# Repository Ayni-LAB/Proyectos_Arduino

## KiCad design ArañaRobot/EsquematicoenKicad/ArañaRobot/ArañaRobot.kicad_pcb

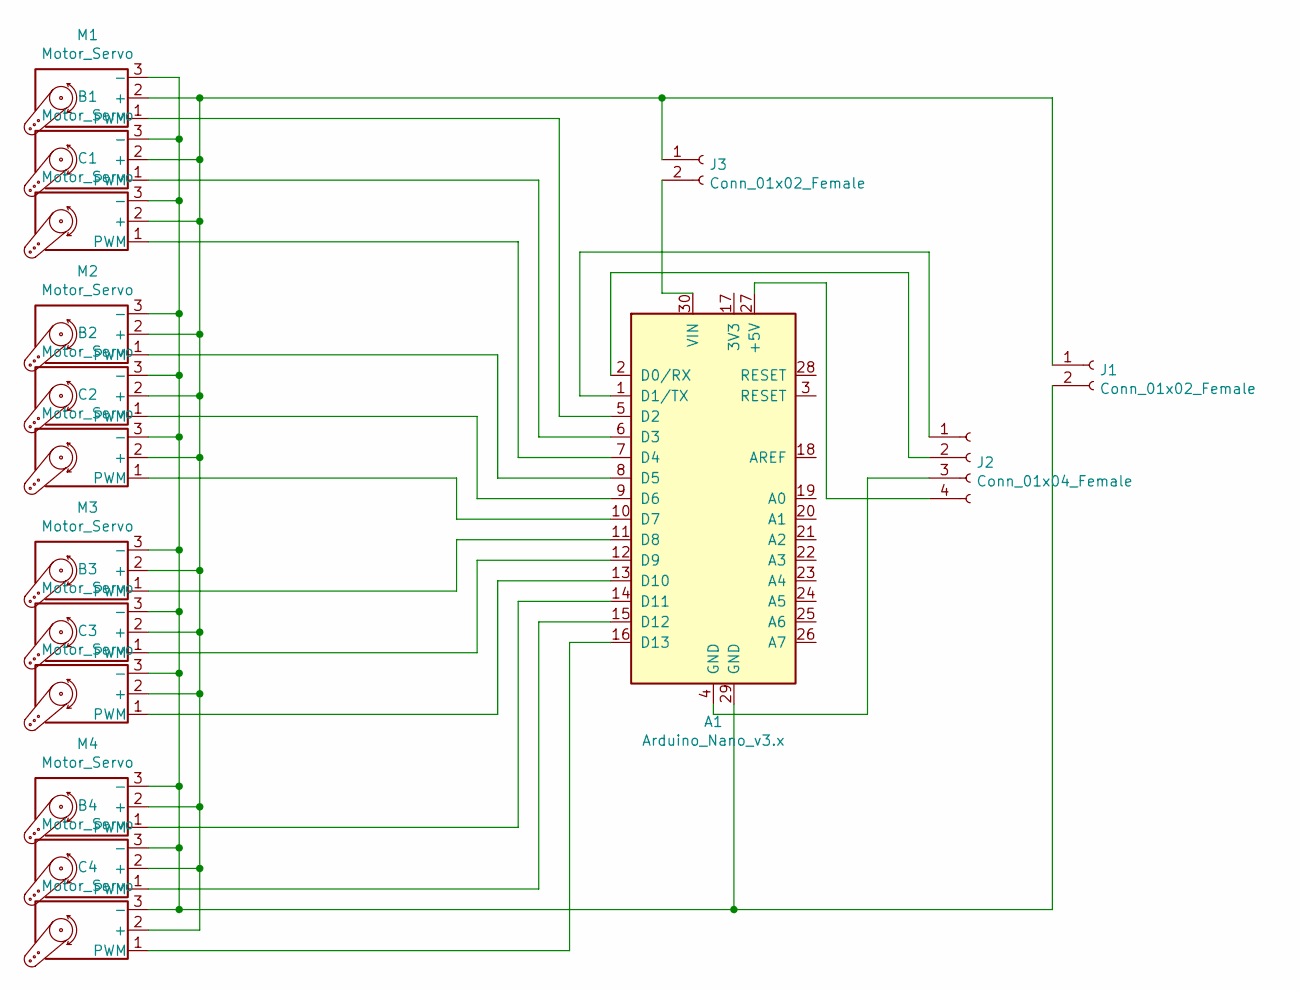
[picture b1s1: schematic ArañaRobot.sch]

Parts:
A1: Arduino_Nano_v3.x; Arduino_Nano
B1, B2, B3, B4: Motor_Servo; PinHeader_1x03_P2.54mm_Vertical
C1, C2, C3, C4: Motor_Servo; PinHeader_1x03_P2.54mm_Vertical
J1: Conn_01x02_Female; PhoenixContact_GMSTBA_2,5_2-G-7,62_1x02_P7.62mm_Horizontal
J2: Conn_01x04_Female; FanPinHeader_1x04_P2.54mm_Vertical
J3: Conn_01x02_Female; PinHeader_1x02_P2.00mm_Vertical
M1, M2, M3, M4: Motor_Servo; PinHeader_1x03_P2.54mm_Vertical

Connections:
unnamed: A1.1 (D1/TX), J2.1
unnamed: A1.2 (D0/RX), J2.2
unnamed: A1.4 (GND), J2.3
unnamed: A1.5 (D2), M1.1 (PWM)
unnamed: A1.6 (D3), B1.1 (PWM)
unnamed: A1.7 (D4), C1.1 (PWM)
unnamed: A1.8 (D5), M2.1 (PWM)
unnamed: A1.9 (D6), B2.1 (PWM)
unnamed: A1.10 (D7), C2.1 (PWM)
unnamed: A1.11 (D8), M3.1 (PWM)
unnamed: A1.12 (D9), B3.1 (PWM)
unnamed: A1.13 (D10), C3.1 (PWM)
unnamed: A1.14 (D11), M4.1 (PWM)
unnamed: A1.15 (D12), B4.1 (PWM)
unnamed: A1.16 (D13), C4.1 (PWM)
unnamed: A1.27 (+5V), J2.4
unnamed: A1.29 (GND), B1.3 (-), B2.3 (-), B3.3 (-), B4.3 (-), C1.3 (-), C2.3 (-), C3.3 (-), C4.3 (-), J1.2, M1.3 (-), M2.3 (-), M3.3 (-), M4.3 (-)
unnamed: A1.30 (VIN), J3.2
unnamed: B1.2 (+), B2.2 (+), B3.2 (+), B4.2 (+), C1.2 (+), C2.2 (+), C3.2 (+), C4.2 (+), J1.1, J3.1, M1.2 (+), M2.2 (+), M3.2 (+), M4.2 (+)

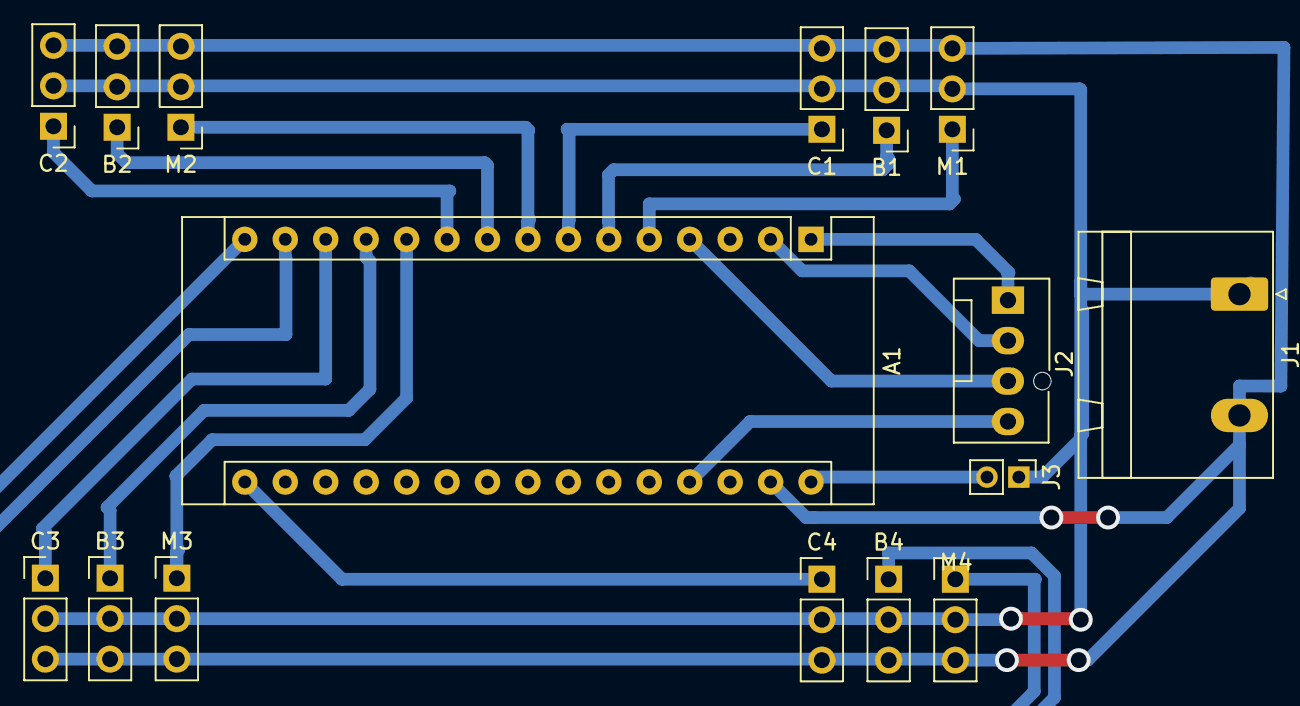
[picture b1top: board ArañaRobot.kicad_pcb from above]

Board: 2 copper layers, 16 parts (0 on the bottom side), 19 nets.

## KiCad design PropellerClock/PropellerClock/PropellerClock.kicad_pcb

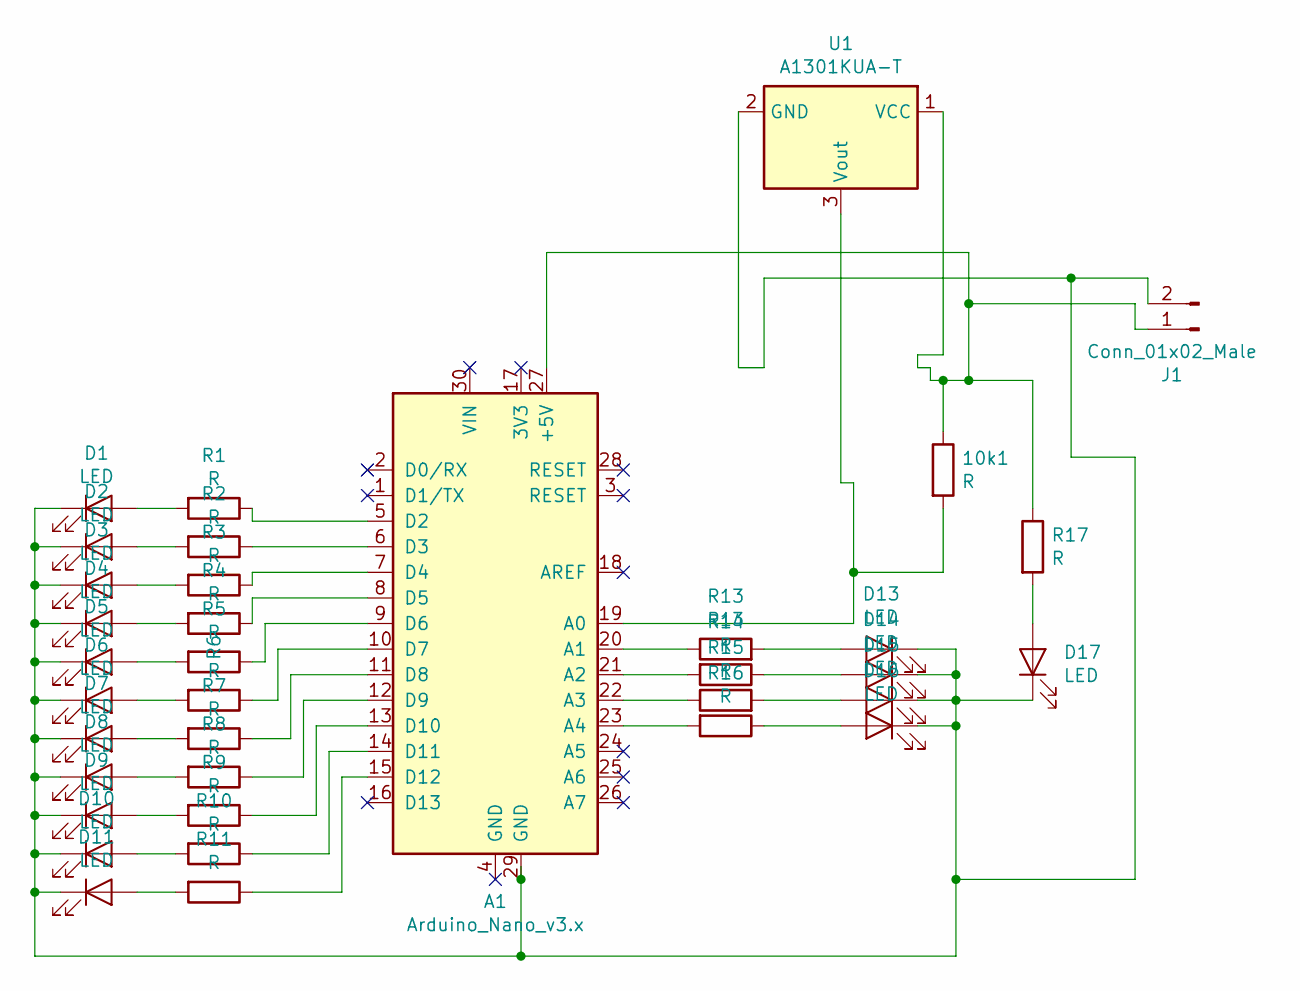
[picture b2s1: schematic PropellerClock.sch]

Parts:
10k1: R; R_Axial_DIN0204_L3.6mm_D1.6mm_P7.62mm_Horizontal
A1: Arduino_Nano_v3.x; Arduino_Nano
D1, D2, D3, D4, D5, D6, D7, D8, D9, D10, D11, D13, D14, D15, D16, D17: LED; LED_D5.0mm
J1: Conn_01x02_Male; PinHeader_1x02_P2.00mm_Vertical
R1, R2, R3, R4, R5, R6, R7, R8, R9, R10, R11, R14, R15, R16, R17: R; R_Axial_DIN0204_L3.6mm_D1.6mm_P7.62mm_Horizontal
R13: R13; R_Axial_DIN0204_L3.6mm_D1.6mm_P7.62mm_Horizontal
U1: A1301KUA-T; PinHeader_1x03_P1.27mm_Vertical

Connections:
unnamed: 10k1.1, A1.27 (+5V), J1.1, R17.1, U1.1 (VCC)
unnamed: 10k1.2, A1.19 (A0), U1.3 (Vout)
unnamed: A1.5 (D2), R1.1
unnamed: A1.6 (D3), R2.1
unnamed: A1.7 (D4), R3.1
unnamed: A1.8 (D5), R4.1
unnamed: A1.9 (D6), R5.1
unnamed: A1.10 (D7), R6.1
unnamed: A1.11 (D8), R7.1
unnamed: A1.12 (D9), R8.1
unnamed: A1.13 (D10), R9.1
unnamed: A1.14 (D11), R10.1
unnamed: A1.15 (D12), R11.1
unnamed: A1.20 (A1), R13.1
unnamed: A1.21 (A2), R14.2
unnamed: A1.22 (A3), R15.1
unnamed: A1.23 (A4), R16.2
unnamed: A1.29 (GND), D1.1 (K), D2.1 (K), D3.1 (K), D4.1 (K), D5.1 (K), D6.1 (K), D7.1 (K), D8.1 (K), D9.1 (K), D10.1 (K), D11.1 (K), D13.1 (K), D14.1 (K), D15.1 (K), D16.1 (K), D17.1 (K), J1.2, U1.2 (GND)
unnamed: D1.2 (A), R1.2
unnamed: D2.2 (A), R2.2
unnamed: D3.2 (A), R3.2
unnamed: D4.2 (A), R4.2
unnamed: D5.2 (A), R5.2
unnamed: D6.2 (A), R6.2
unnamed: D7.2 (A), R7.2
unnamed: D8.2 (A), R8.2
unnamed: D9.2 (A), R9.2
unnamed: D10.2 (A), R10.2
unnamed: D11.2 (A), R11.2
unnamed: D13.2 (A), R13.2
unnamed: D14.2 (A), R14.1
unnamed: D15.2 (A), R15.2
unnamed: D16.2 (A), R16.1
unnamed: D17.2 (A), R17.2

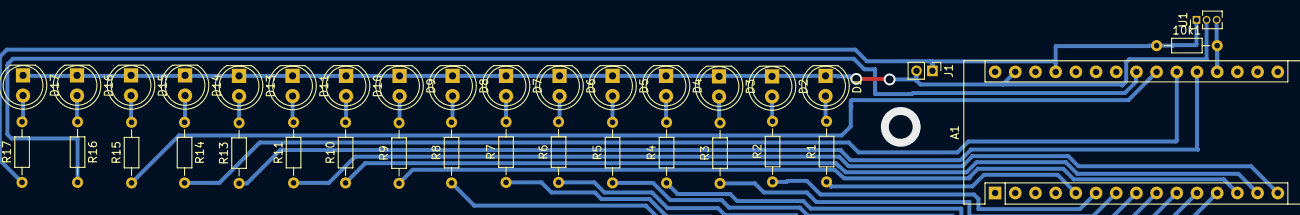
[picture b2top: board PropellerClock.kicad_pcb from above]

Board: 2 copper layers, 36 parts (0 on the bottom side), 34 nets.

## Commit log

2020-03-02 inicio
2020-03-02 1 modificacion readme
2020-03-02 1 modificacion codigo araña
2020-03-02 Comentarios Araña
2020-03-02 Cambio en comentarios
2020-03-02 Camb. Lagarto
2020-03-02 modificaciones Br
2020-03-02 prueba de contri
2020-03-02 Prueba commit
2020-03-02 Commibrig
2020-03-02 modificaciones bases
2020-03-03 Proyecto nuevo
2020-03-03 AgregandoFotos
2020-03-03 Readme modificado
2020-03-03 Readme imagenes
2020-03-03 readme configurations
2020-03-03 Readme1
2020-03-03 Readme3
2020-03-03 Readme4
2020-03-03 Readme
2020-03-03 Readme5
2020-03-11 Primer commit
2020-03-11 Propeller prototipo
2020-03-11 edit
2020-03-11 edit2
2020-03-11 edit3
2020-03-11 edit4
2020-03-12 refresh
2020-03-13 lagarto
2020-03-15 EditLagar
2020-03-15 EditLagar (#2)
2020-03-15 Revert "EditLagar (#2)"
    This reverts commit 055c49ebf7e1ec19fa1edd763d7685f3391a3515.
